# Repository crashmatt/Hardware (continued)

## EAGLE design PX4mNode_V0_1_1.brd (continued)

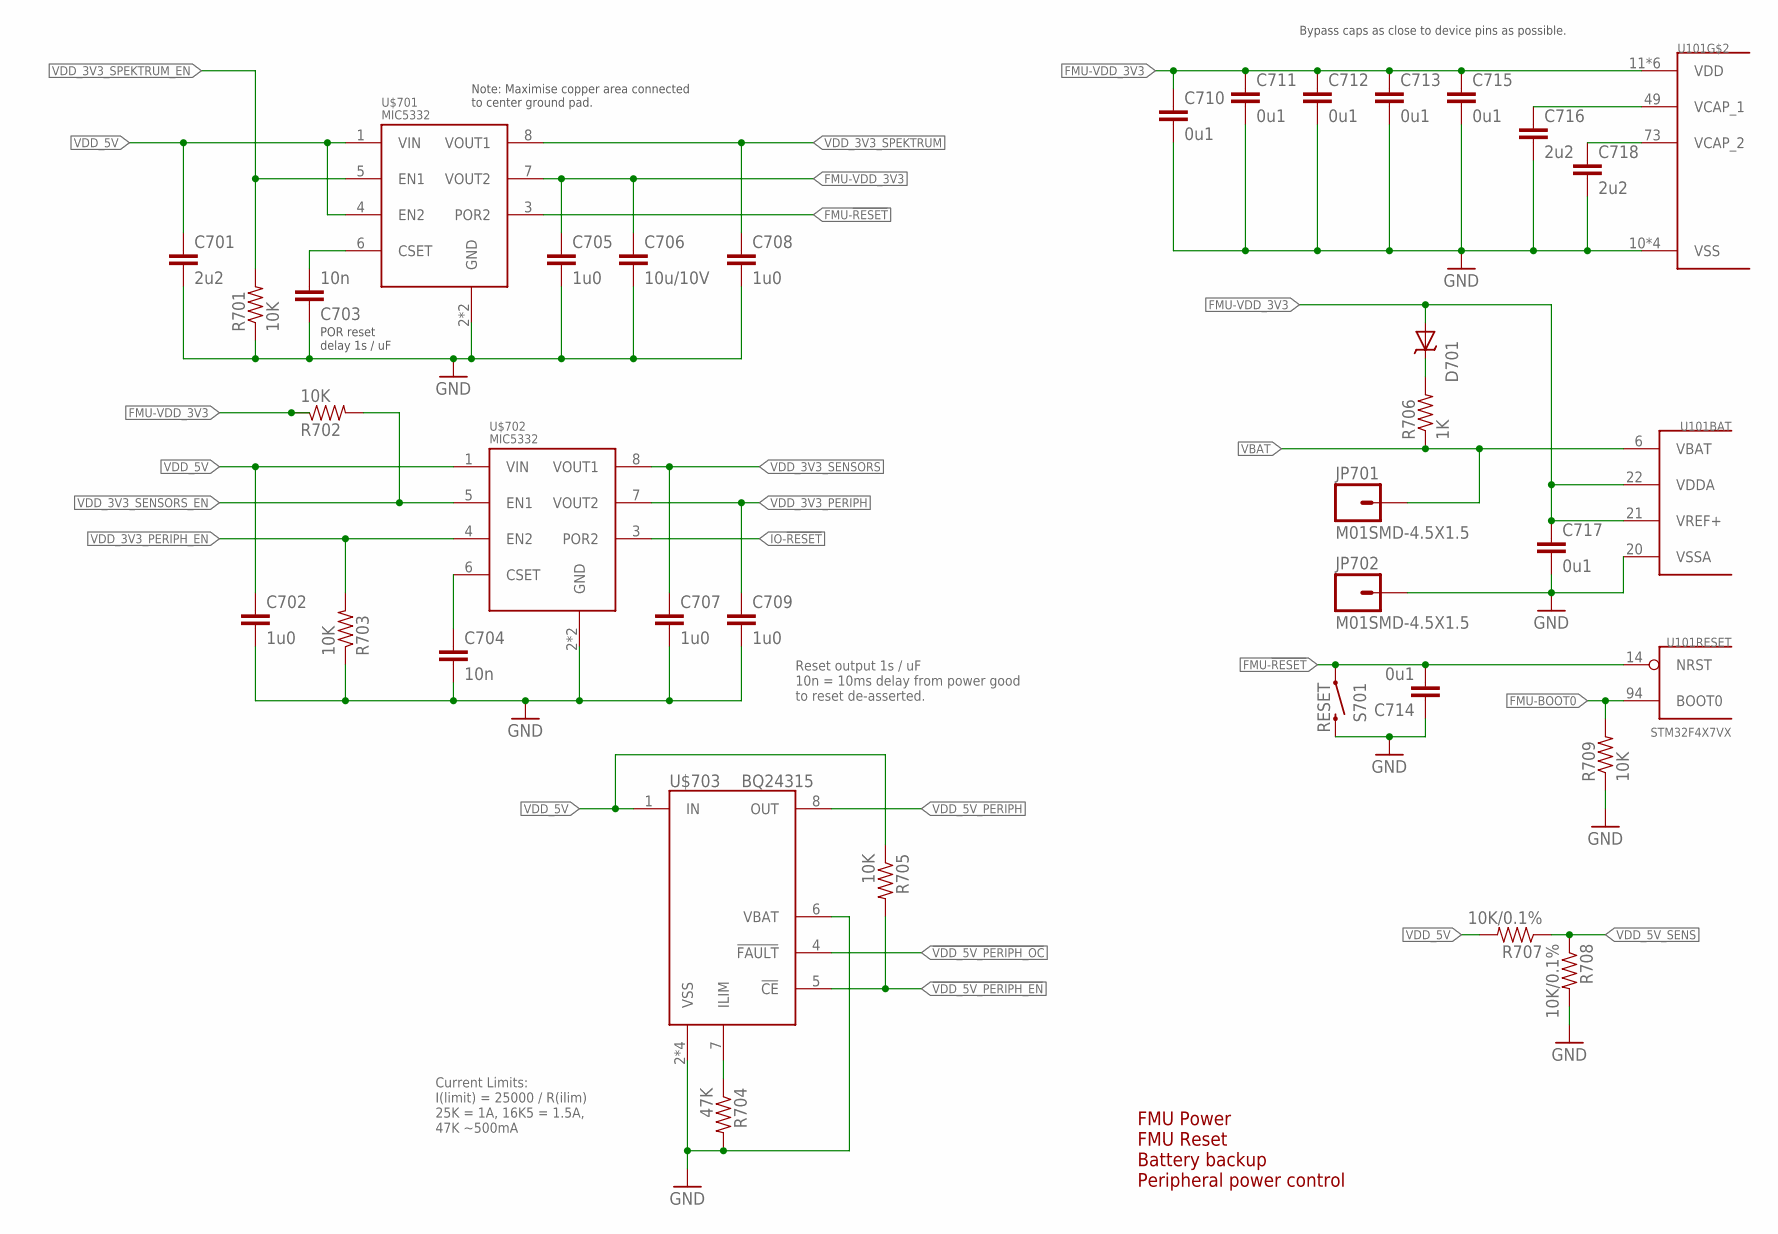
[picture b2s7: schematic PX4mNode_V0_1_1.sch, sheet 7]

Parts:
C701, C716, C718: 2u2; 0603-CAP; PARTNO C1608Y5V1C225Z
C702, C705, C707, C708, C709: 1u0; 0603-CAP; PARTNO CC0603ZRY5V7BB105
C703, C704: 10n; 0402-CAP; PARTNO CC0402KRX7R7BB103
C706: 10u/10V; 0805-CAP; PARTNO CC0805ZKY5V6BB106
C710, C711, C712, C713, C714, C715, C717: 0u1; 0402-CAP; PARTNO CC0402ZRY5V7BB104
D701: MSS1P4-M3; MICROSMP; PARTNO MSS1P4-M3/89A
JP701, JP702: M01SMD-4.5X1.5; PAD-1.5X4.5
R701, R702, R703, R705, R709: 10K; 0402-RES; PARTNO RC0402FR-0710KL
R704: 47K; 0402-RES; PARTNO RMCF0402FT47K
R706: 1K; 0402-RES; PARTNO RC0402FR-071KL
R707, R708: 10K/0.1%; 0402-RES; PARTNO ERA-2AEB103X
S701: RESET; EVQP7J01K; PARTNO EVQP7J01K
U101: STM32F4X7VX; TQFP100; PARTNO STM32F427VI
U$701, U$702: MIC5332; MLF-8-EPAD; PARTNO MIC5332-SSYMT
U$703: BQ24315; QFN8-DSG; PARTNO BQ24315DSGR

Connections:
!VDD_5V_PERIPH_EN: R705.P$2 (2), U$703.5 (!CE); also elsewhere on the board
!VDD_5V_PERIPH_OC: U$703.4 (!FAULT); also elsewhere on the board
FMU-!RESET: C714.P$2 (2), S701.A1 (1), U101.14 (NRST), U$701.3 (POR2); also elsewhere on the board
FMU-BOOT0: R709.P$2 (2), U101.94 (BOOT0); also elsewhere on the board
FMU-VDD_3V3: C705.P$1 (1), C706.P$1 (1), C710.P$1 (1), C711.P$1 (1), C712.P$1 (1), C713.P$1 (1), C715.P$1 (1), C717.P$1 (1), D701.ANODE (A), R702.P$1 (1), U101.11 (VDD), U101.19 (VDD), U101.21 (VREF+), U101.22 (VDDA), U101.28 (VDD), U101.50 (VDD), U101.75 (VDD), U101.100 (VDD), U$701.7 (VOUT2); also elsewhere on the board
GND: C701.P$2 (2), C702.P$2 (2), C703.P$1 (1), C704.P$2 (2), C705.P$2 (2), C706.P$2 (2), C707.P$2 (2), C708.P$2 (2), C709.P$2 (2), C710.P$2 (2), C711.P$2 (2), C712.P$2 (2), C713.P$2 (2), C714.P$1 (1), C715.P$2 (2), C716.P$2 (2), C717.P$2 (2), C718.P$2 (2), JP702.P$1, R701.P$1 (1), R703.P$1 (1), R704.P$2 (2), R708.P$2 (2), R709.P$1 (1), S701.B3 (2), U101.10 (VSS), U101.20 (VSSA), U101.27 (VSS), U101.74 (VSS), U101.99 (VSS), U$701.2 (GND), U$701.GND, U$702.2 (GND), U$702.GND, U$703.2 (VSS), U$703.6 (VBAT), U$703.GND (VSS), U$703.P$2 (VSS), U$703.P$3 (VSS); also elsewhere on the board
IO-!RESET: U$702.3 (POR2)
unnamed: C718.P$1 (1), U101.73 (VCAP_2)
unnamed: D701.CATHODE (C), R706.P$2 (2)
unnamed: C703.P$2 (2), U$701.6 (CSET)
unnamed: C716.P$1 (1), U101.49 (VCAP_1)
unnamed: R704.P$1 (1), U$703.7 (ILIM)
unnamed: C704.P$1 (1), U$702.6 (CSET)
VBAT: JP701.P$1, R706.P$1 (1), U101.6 (VBAT)
VDD_3V3_PERIPH: C709.P$1 (1), U$702.7 (VOUT2)
VDD_3V3_PERIPH_EN: R703.P$2 (2), U$702.4 (EN2)
VDD_3V3_SENSORS: C707.P$1 (1), U$702.8 (VOUT1); also elsewhere on the board
VDD_3V3_SENSORS_EN: R702.P$2 (2), U$702.5 (EN1); also elsewhere on the board
VDD_3V3_SPEKTRUM: C708.P$1 (1), U$701.8 (VOUT1); also elsewhere on the board
VDD_3V3_SPEKTRUM_EN: R701.P$2 (2), U$701.5 (EN1); also elsewhere on the board
VDD_5V: C701.P$1 (1), C702.P$1 (1), R705.P$1 (1), R707.P$2 (2), U$701.1 (VIN), U$701.4 (EN2), U$702.1 (VIN), U$703.1 (IN); also elsewhere on the board
VDD_5V_PERIPH: U$703.8 (OUT); also elsewhere on the board
VDD_5V_SENS: R707.P$1 (1), R708.P$1 (1); also elsewhere on the board

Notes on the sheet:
FMU Power FMU Reset Battery backup Peripheral power control
Bypass caps as close to device pins as possible.
Note: Maximise copper area connected to center ground pad.
POR reset delay 1s / uF
Current Limits: I(limit) = 25000 / R(ilim) 25K = 1A, 16K5 = 1.5A, 47K ~500mA
Reset output 1s / uF 10n = 10ms delay from power good to reset de-asserted.

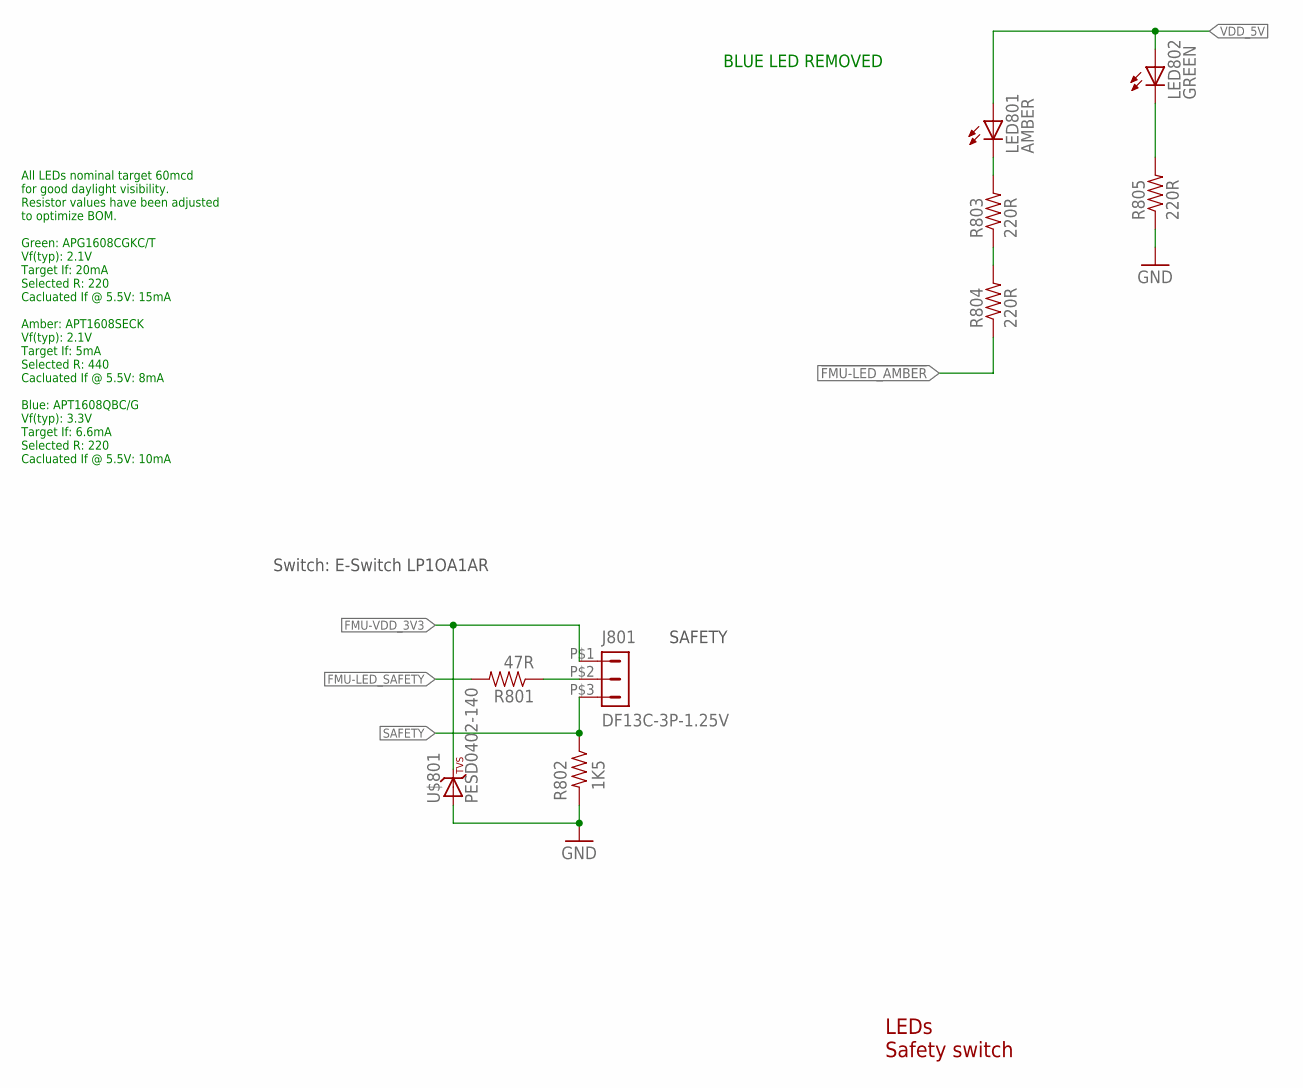
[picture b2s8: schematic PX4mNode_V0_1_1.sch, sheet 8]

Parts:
J801: DF13C-3P-1.25V; PARTNO DF13C-3P-1.25V(20)
LED801: AMBER; 0603-LED; PARTNO APTD1608SECK
LED802: GREEN; 0603-LED; PARTNO APTD1608CGCK
R801: 47R; 0402-RES; PARTNO RC0402JR-0747RL
R802: 1K5; 0402-RES; PARTNO RC0402FR-071K5L
R803, R804, R805: 220R; 0402-RES; PARTNO RC0402FR-07220RL
U$801: PESD0402-140; 0402-TVS; PARTNO PESD0402-140

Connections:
!FMU-LED_AMBER: R804.P$1 (1); also elsewhere on the board
FMU-LED_SAFETY: R801.P$2 (2)
FMU-VDD_3V3: J801.P$1 (1), U$801.C; also elsewhere on the board
GND: R802.P$2 (2), R805.P$1 (1), U$801.A; also elsewhere on the board
unnamed: LED802.C, R805.P$2 (2)
unnamed: R803.P$1 (1), R804.P$2 (2)
unnamed: LED801.C, R803.P$2 (2)
unnamed: J801.P$2 (2), R801.P$1 (1)
SAFETY: J801.P$3 (3), R802.P$1 (1)
VDD_5V: LED801.A, LED802.A; also elsewhere on the board

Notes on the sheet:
LEDs Safety switch
Switch: E-Switch LP1OA1AR
SAFETY
All LEDs nominal target 60mcd for good daylight visibility. Resistor values have been adjusted to optimize BOM. Green: APG1608CGKC/T Vf(typ): 2.1V Target If: 20mA Selected R: 220 Cacluated If @ 5.5V: 15mA Amber: APT1608SECK Vf(typ): 2.1V Target If: 5mA Selected R: 440 Cacluated If @ 5.5V: 8mA Blue: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
BLUE LED REMOVED

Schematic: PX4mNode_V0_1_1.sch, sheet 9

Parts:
D901: DIODESOD; SOD-323
D902, D903: B340A; SMA-DIODE; PARTNO B340A
D904: MSS1P4-M3; MICROSMP; PARTNO MSS1P4-M3/89A
JP901: M02PTH3; 1X02_LONGPADS
R901, R902, R903: 10K/0.1%; 0402-RES; PARTNO ERA-2AEB103X

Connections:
GND: D901.2 (A), JP901.2, R903.P$1 (1); also elsewhere on the board
unnamed: D901.1 (C), R901.P$1 (1), R902.P$2 (2)
VBUS: D904.ANODE (A); also elsewhere on the board
VDD_IN: D902.C, D903.C, D904.CATHODE (C); also elsewhere on the board
VDD_SERVO_SENS: R902.P$1 (1), R903.P$2 (2)
V_EXT: D903.A, JP901.1, R901.P$2 (2)
V_SERVO: D902.A; also elsewhere on the board

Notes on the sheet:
IO SoC Ports Spektrum/DSM port
Timer allocation: PA0: TIM2_CH1: IO-CH1 PA1: TIM2_CH2: IO-CH2 PB8: TIM4_CH3: IO-CH3 PB9: TIM4_CH4: IO-CH4 PA6: TIM3_CH1: IO-CH5 PA7: TIM3_CH2: IO-CH6 PB0: TIM3_CH3: IO-CH7 PB1: TIM3_CH4: IO-CH8 PA8: TIM1_CH1: PPM_IN PA11: TIM1_CH4: RSSI_IN
DO NOT FIT

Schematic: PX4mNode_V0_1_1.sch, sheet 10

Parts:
J1001: SERVO_HEADER-3X8; 3X8RA_SERVO
JP1001, JP1002: M01SMD-4.5X1.5; PAD-1.5X4.5
L1001: NUF8402MN; DFN16-THIN
R1001, R1002: 220R; 0402-RES; PARTNO RC0402FR-07220RL

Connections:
FMU-CH1: L1001.P$1; also elsewhere on the board
FMU-CH1-PROT: J1001.S1, L1001.P$16
FMU-CH2: L1001.P$2; also elsewhere on the board
FMU-CH3: L1001.P$3; also elsewhere on the board
FMU-CH4: L1001.P$4; also elsewhere on the board
FMU-CH5: L1001.P$5; also elsewhere on the board
FMU-CH6: L1001.P$6; also elsewhere on the board
FMU-CH7: L1001.P$7; also elsewhere on the board
FMU-CH8: L1001.P$8; also elsewhere on the board
FMU-CH9: R1001.P$2 (2); also elsewhere on the board
FMU-CH10: R1002.P$2 (2); also elsewhere on the board
GND: J1001.GND_S1, J1001.GND_S2, J1001.GND_S3, J1001.GND_S4, J1001.GND_S5, J1001.GND_S6, J1001.GND_S7, J1001.GND_S8, L1001.P$EP (GND); also elsewhere on the board
unnamed: J1001.S8, L1001.P$9
unnamed: J1001.S7, L1001.P$10
unnamed: JP1001.P$1, R1001.P$1 (1)
unnamed: JP1002.P$1, R1002.P$1 (1)
unnamed: J1001.S6, L1001.P$11
unnamed: J1001.S5, L1001.P$12
unnamed: J1001.S4, L1001.P$13
unnamed: J1001.S3, L1001.P$14
unnamed: J1001.S2, L1001.P$15
V_SERVO: J1001.PWR_S1, J1001.PWR_S2, J1001.PWR_S3, J1001.PWR_S4, J1001.PWR_S5, J1001.PWR_S6, J1001.PWR_S7, J1001.PWR_S8; also elsewhere on the board

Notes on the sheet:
Servo Header S.Bus interface
Servo outputs

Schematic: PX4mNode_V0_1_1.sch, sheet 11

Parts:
BOOT: PAD.04; PAD.04X.04; PARTNO *
JP1101, JP1102, JP1103, JP1104: FIDUCIAL1.5X3; FIDUCIAL-1.5X3; PARTNO *
M3_MOUNT1101, M3_MOUNT1102, M3_MOUNT1103, M3_MOUNT1104: MOUNT-HOLE3.1MM; MOUNT-HOLE3.1; PARTNO *
OSHW_LOGO: OSHW-LOGOS; OSHW-LOGO-S; PARTNO *

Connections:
FMU-BOOT0: BOOT.P$1; also elsewhere on the board

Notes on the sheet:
Mounting holes to suit M3 fastener
and Richco R908 series spacer.
Use R908-5 spacers to stack with
other PX4 series boards (7.95 mm).
Production Testing Pads
Test and Fiducials
Minimum drill: 0.3 mm
Minimum trace width (use mm for traces): 0.15 mm
Minimum copper distance (all signals): 0.15 mm
Dimension / hole minimum distance: 0.2 mm
Layout grid: 4 mil, part grid: 4 mil. Dimensions / hole positions: 0.5 mm
Board: FR4 black, 1.0 mm. Solder stop on vias < 0.6 mm.
Signoff rules: Footprint checked, pinmap checked, schematic checked, cross-references to other pages checked.
Routing: 1: general/escape 2: ground 3: horizontal 4: vertical 5: power 6: general/escape
Fiducials for machine vision alignment.

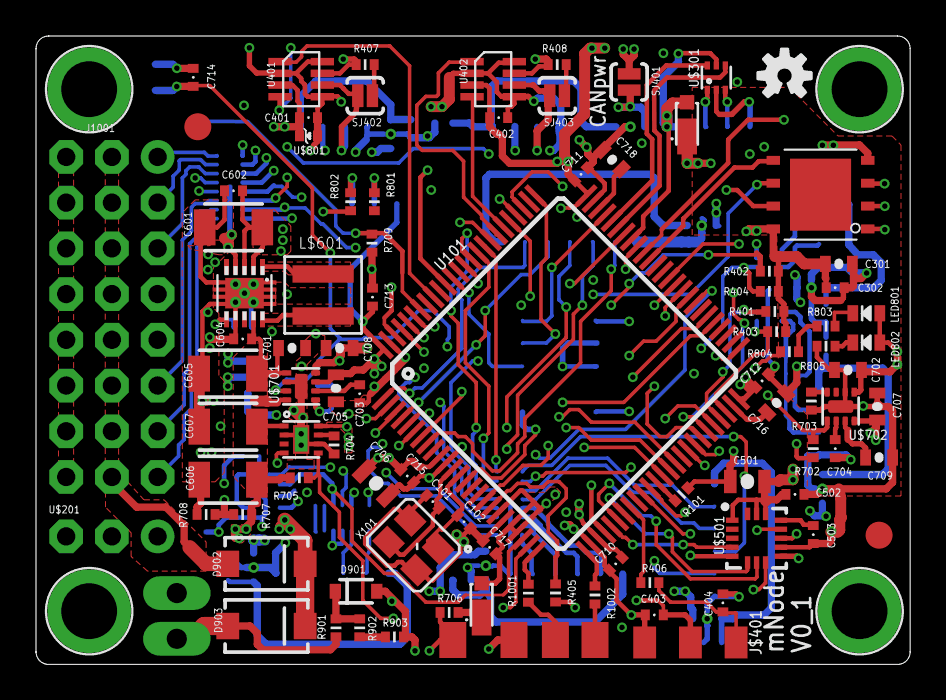
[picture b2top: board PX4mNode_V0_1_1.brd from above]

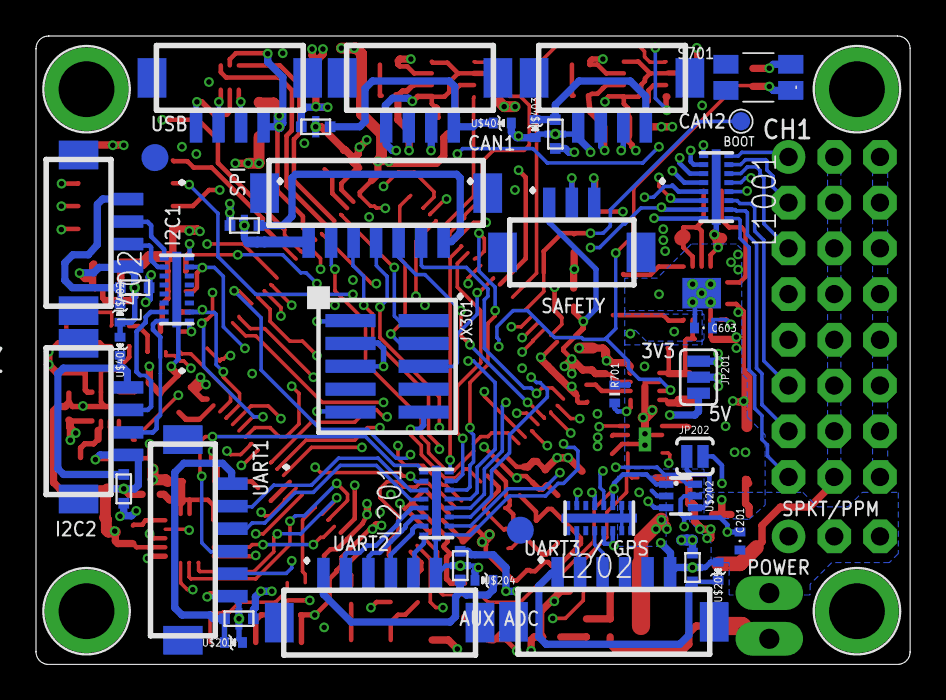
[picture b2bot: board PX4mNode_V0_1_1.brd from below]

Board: 6 copper layers, 48.6 x 34.9 mm, 140 parts (40 on the bottom side), 144 nets.

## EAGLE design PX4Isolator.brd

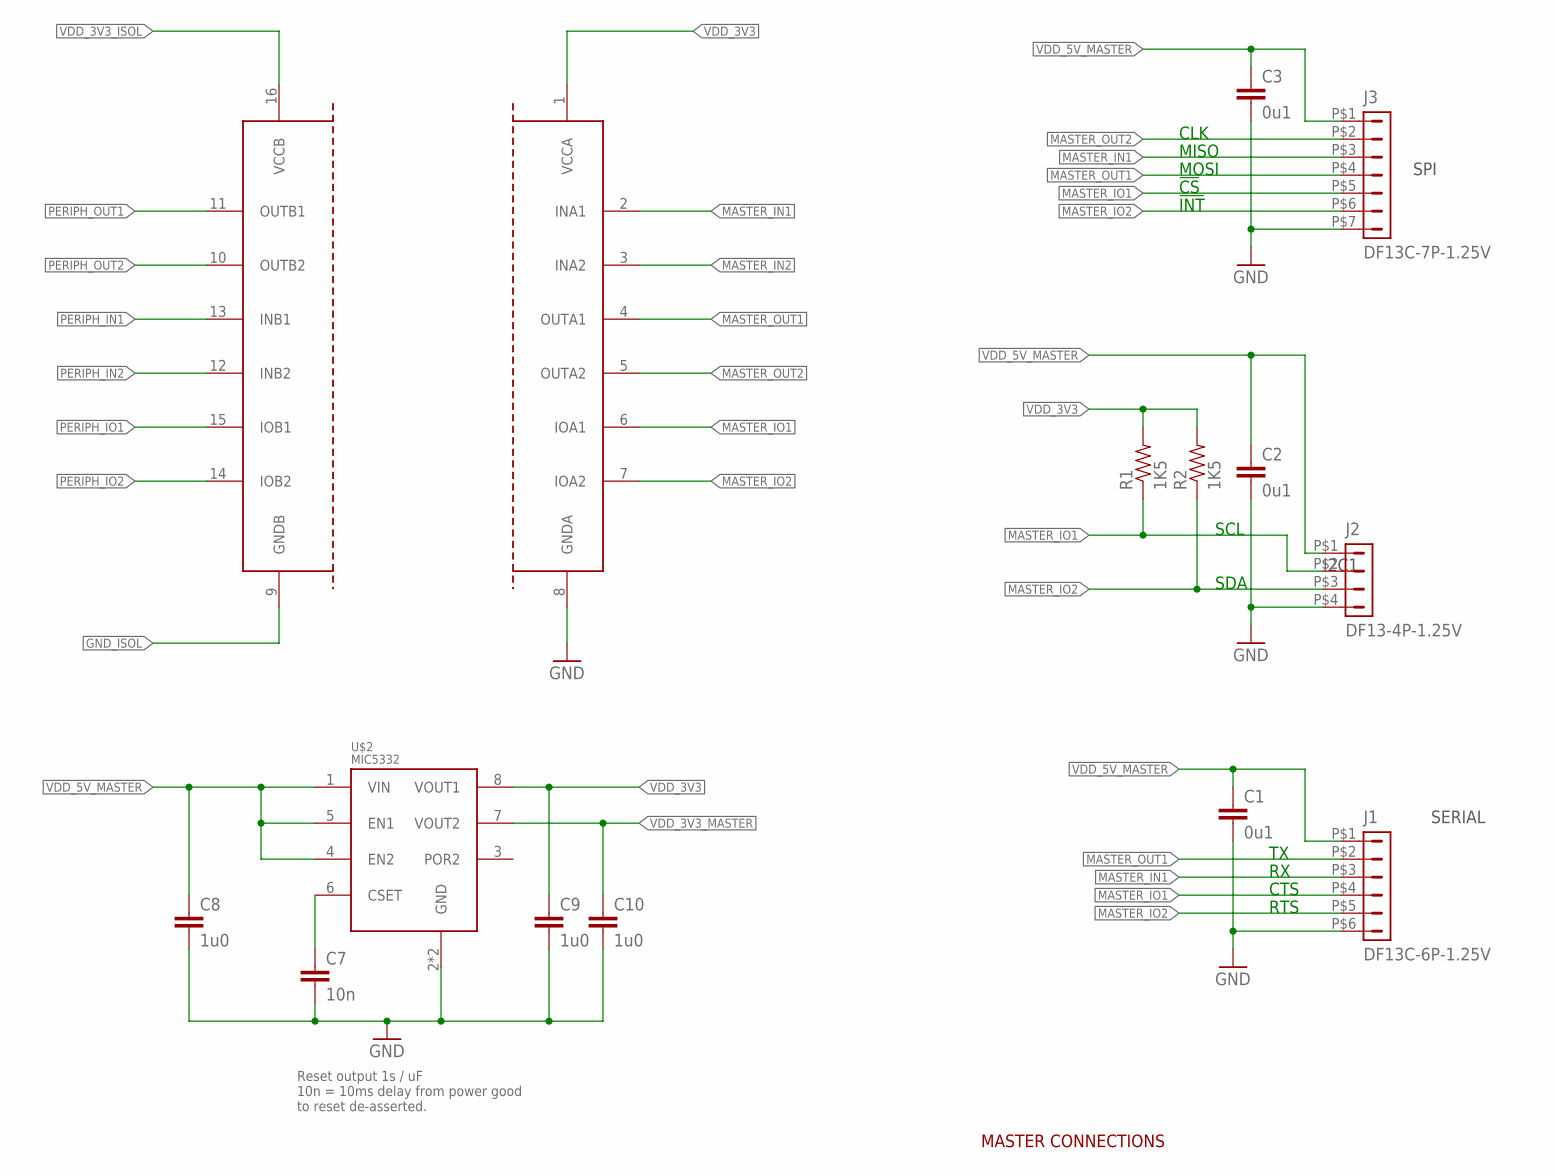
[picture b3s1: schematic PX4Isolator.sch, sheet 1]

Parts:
C1, C2, C3: 0u1; 0402-CAP; PARTNO CC0402ZRY5V7BB104
C7: 10n; 0402-CAP; PARTNO CC0402KRX7R7BB103
C8, C9, C10: 1u0; 0603-CAP; PARTNO CC0603ZRY5V7BB105
J1: DF13C-6P-1.25V; PARTNO DF13C-6P-1.25V(20)
J2: DF13-4P-1.25V; DF13C-4P-1.25V; PARTNO DF13C-4P-1.25V(20)
J3: DF13C-7P-1.25V; PARTNO DF13C-7P-1.25V(20)
R1, R2: 1K5; 0402-RES; PARTNO RC0402FR-071K5L
U$1: MAX14850; SOIC16
U$2: MIC5332; MLF-8-EPAD; PARTNO MIC5332-SSYMT

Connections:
GND: C1.P$2 (2), C2.P$2 (2), C3.P$2 (2), C7.P$2 (2), C8.P$2 (2), C9.P$2 (2), C10.P$2 (2), J1.P$6 (6), J2.P$4 (4), J3.P$7 (7), U$1.8 (GNDA), U$2.2 (GND), U$2.GND; also elsewhere on the board
GND_ISOL: U$1.9 (GNDB); also elsewhere on the board
MASTER_IN1: J1.P$3 (3), J3.P$3 (3), U$1.2 (INA1)
MASTER_IN2: U$1.3 (INA2)
MASTER_IO1: J1.P$4 (4), J2.P$2 (2), J3.P$5 (5), R1.P$1 (1), U$1.6 (IOA1)
MASTER_IO2: J1.P$5 (5), J2.P$3 (3), J3.P$6 (6), R2.P$1 (1), U$1.7 (IOA2)
MASTER_OUT1: J1.P$2 (2), J3.P$4 (4), U$1.4 (OUTA1)
MASTER_OUT2: J3.P$2 (2), U$1.5 (OUTA2)
unnamed: C7.P$1 (1), U$2.6 (CSET)
PERIPH_IN1: U$1.13 (INB1); also elsewhere on the board
PERIPH_IN2: U$1.12 (INB2)
PERIPH_IO1: U$1.15 (IOB1); also elsewhere on the board
PERIPH_IO2: U$1.14 (IOB2); also elsewhere on the board
PERIPH_OUT1: U$1.11 (OUTB1); also elsewhere on the board
PERIPH_OUT2: U$1.10 (OUTB2); also elsewhere on the board
VDD_3V3: C9.P$1 (1), R1.P$2 (2), R2.P$2 (2), U$1.1 (VCCA), U$2.8 (VOUT1); also elsewhere on the board
VDD_3V3_ISOL: U$1.16 (VCCB); also elsewhere on the board
VDD_3V3_MASTER: C10.P$1 (1), U$2.7 (VOUT2)
VDD_5V_MASTER: C1.P$1 (1), C2.P$1 (1), C3.P$1 (1), C8.P$1 (1), J1.P$1 (1), J2.P$1 (1), J3.P$1 (1), U$2.1 (VIN), U$2.4 (EN2), U$2.5 (EN1)

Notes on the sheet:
SPI
MASTER CONNECTIONS
I2C1
SERIAL
CLK
MISO
MOSI
!CS
!INT
SCL
SDA
CTS
RTS
Reset output 1s / uF 10n = 10ms delay from power good to reset de-asserted.

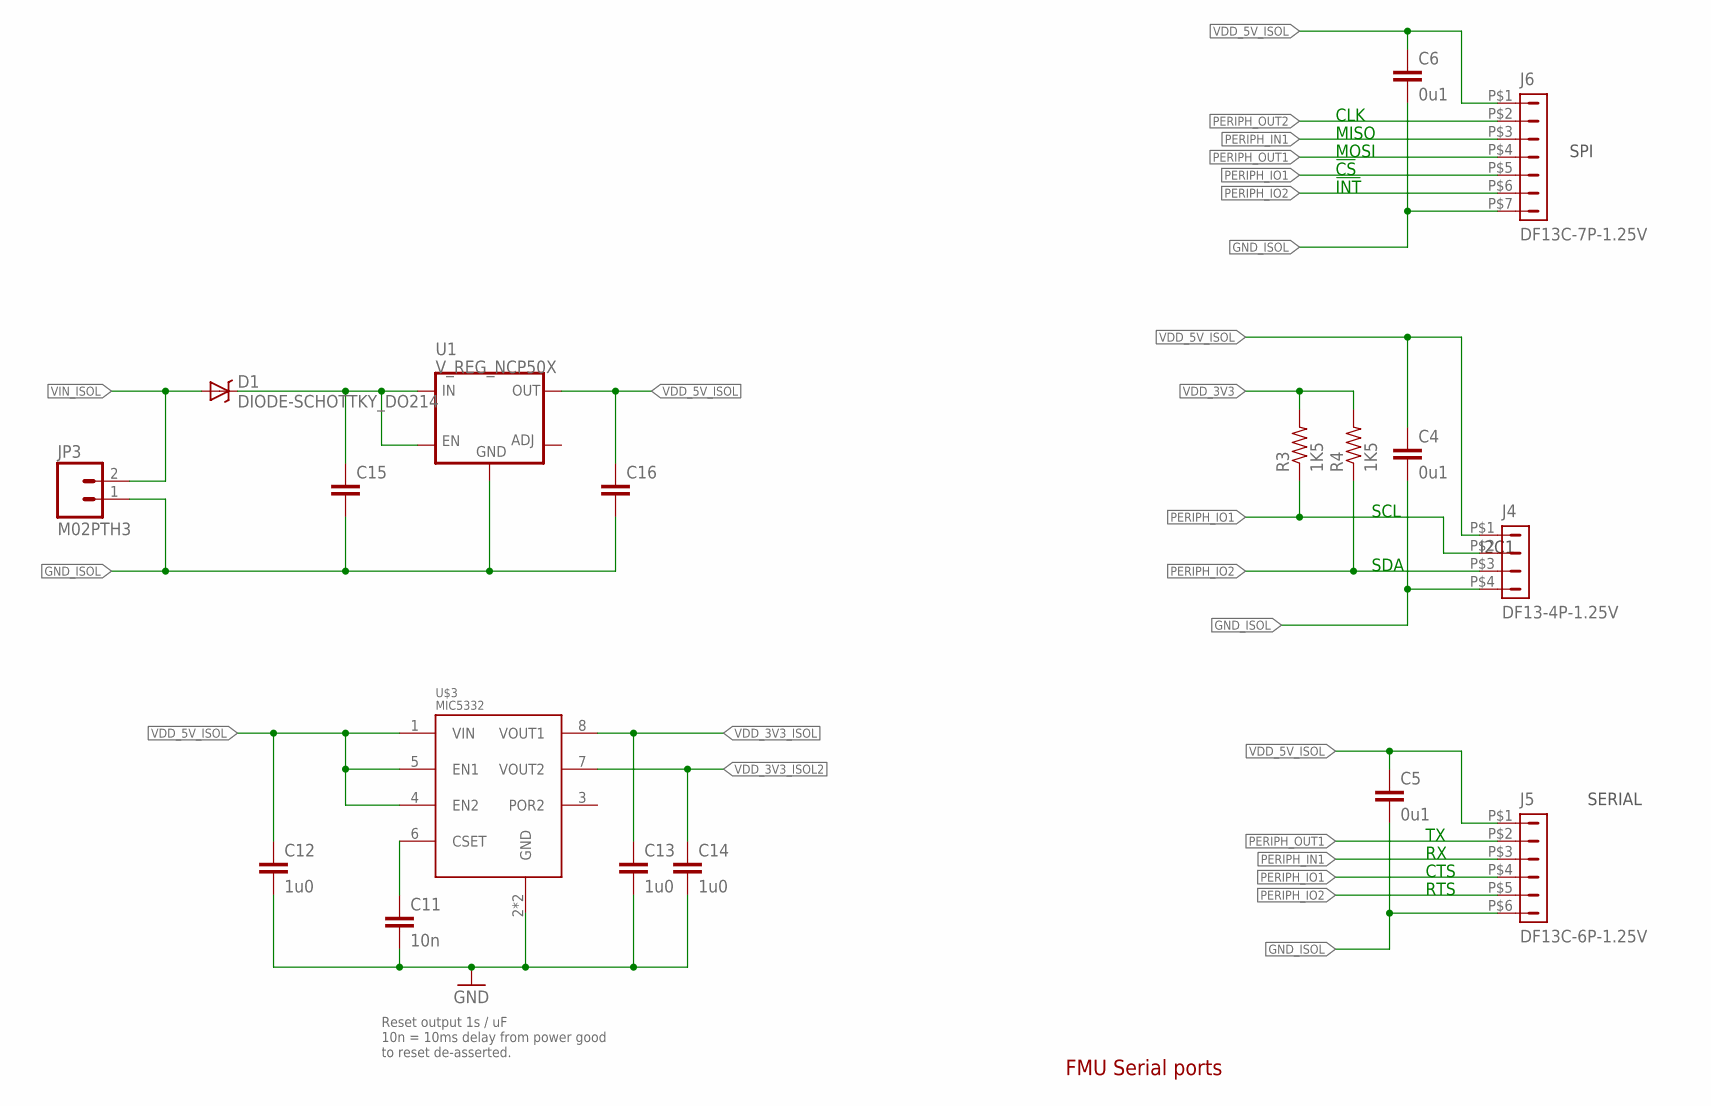
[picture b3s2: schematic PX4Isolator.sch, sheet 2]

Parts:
C4, C5, C6: 0u1; 0402-CAP; PARTNO CC0402ZRY5V7BB104
C11: 10n; 0402-CAP; PARTNO CC0402KRX7R7BB103
C12, C13, C14: 1u0; 0603-CAP; PARTNO CC0603ZRY5V7BB105
C15, C16: CAP0603; 0603-CAP
D1: DIODE-SCHOTTKY_DO214; DO214AC
J4: DF13-4P-1.25V; DF13C-4P-1.25V; PARTNO DF13C-4P-1.25V(20)
J5: DF13C-6P-1.25V; PARTNO DF13C-6P-1.25V(20)
J6: DF13C-7P-1.25V; PARTNO DF13C-7P-1.25V(20)
JP3: M02PTH3; 1X02_LONGPADS
R3, R4: 1K5; 0402-RES; PARTNO RC0402FR-071K5L
U1: V_REG_NCP50X; DPAK-5
U$3: MIC5332; MLF-8-EPAD; PARTNO MIC5332-SSYMT

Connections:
GND: C11.P$2 (2), C12.P$2 (2), C13.P$2 (2), C14.P$2 (2), U$3.2 (GND), U$3.GND; also elsewhere on the board
GND_ISOL: C4.P$2 (2), C5.P$2 (2), C6.P$2 (2), C15.P$2 (2), C16.P$2 (2), J4.P$4 (4), J5.P$6 (6), J6.P$7 (7), JP3.1, U1.GND; also elsewhere on the board
unnamed: C11.P$1 (1), U$3.6 (CSET)
unnamed: C15.P$1 (1), D1.C, U1.EN, U1.VIN (IN)
PERIPH_IN1: J5.P$3 (3), J6.P$3 (3); also elsewhere on the board
PERIPH_IO1: J4.P$2 (2), J5.P$4 (4), J6.P$5 (5), R3.P$1 (1); also elsewhere on the board
PERIPH_IO2: J4.P$3 (3), J5.P$5 (5), J6.P$6 (6), R4.P$1 (1); also elsewhere on the board
PERIPH_OUT1: J5.P$2 (2), J6.P$4 (4); also elsewhere on the board
PERIPH_OUT2: J6.P$2 (2); also elsewhere on the board
VDD_3V3: R3.P$2 (2), R4.P$2 (2); also elsewhere on the board
VDD_3V3_ISOL: C13.P$1 (1), U$3.8 (VOUT1); also elsewhere on the board
VDD_3V3_ISOL2: C14.P$1 (1), U$3.7 (VOUT2)
VDD_5V_ISOL: C4.P$1 (1), C5.P$1 (1), C6.P$1 (1), C12.P$1 (1), C16.P$1 (1), J4.P$1 (1), J5.P$1 (1), J6.P$1 (1), U1.VOUT (OUT), U$3.1 (VIN), U$3.4 (EN2), U$3.5 (EN1)
VIN_ISOL: D1.A, JP3.2

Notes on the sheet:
FMU Serial ports
SPI
I2C1
SERIAL
CLK
MISO
MOSI
!CS
!INT
SCL
SDA
CTS
RTS
Reset output 1s / uF 10n = 10ms delay from power good to reset de-asserted.

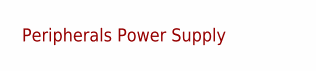
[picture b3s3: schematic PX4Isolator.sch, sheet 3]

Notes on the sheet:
Peripherals Power Supply

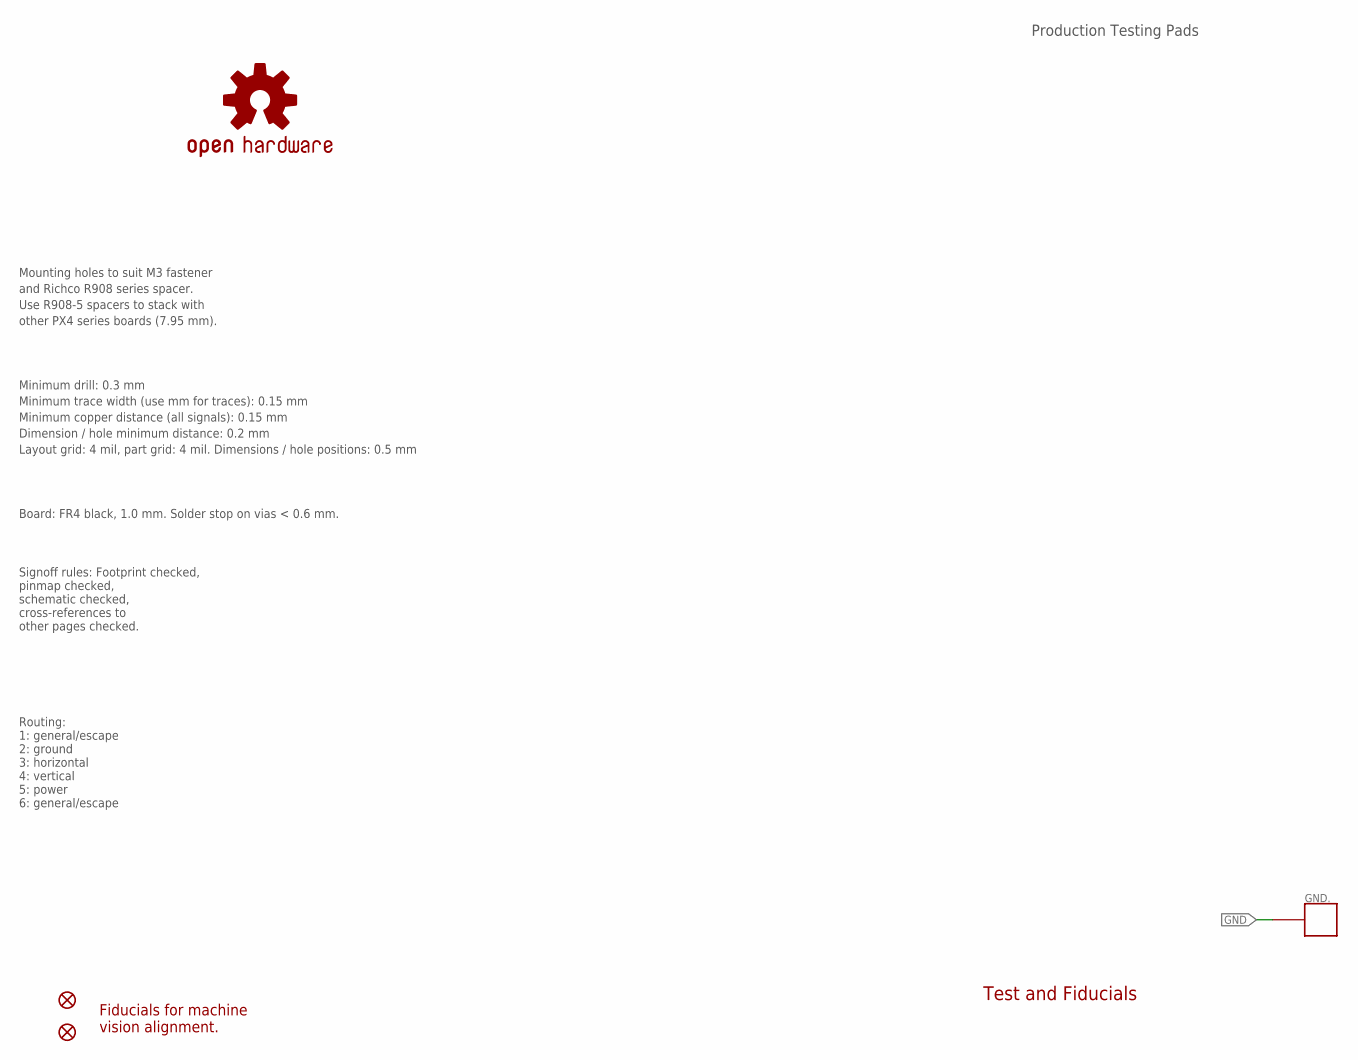
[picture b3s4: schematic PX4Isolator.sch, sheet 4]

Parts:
GND.: PAD.04; PAD.04X.04; PARTNO *
JP1, JP2: FIDUCIAL1.5X3; FIDUCIAL-1.5X3; PARTNO *
OSHW_LOGO: OSHW-LOGOS; OSHW-LOGO-S; PARTNO *

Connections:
GND: GND..P$1; also elsewhere on the board

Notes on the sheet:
Mounting holes to suit M3 fastener
and Richco R908 series spacer.
Use R908-5 spacers to stack with
other PX4 series boards (7.95 mm).
Production Testing Pads
Test and Fiducials
Minimum drill: 0.3 mm
Minimum trace width (use mm for traces): 0.15 mm
Minimum copper distance (all signals): 0.15 mm
Dimension / hole minimum distance: 0.2 mm
Layout grid: 4 mil, part grid: 4 mil. Dimensions / hole positions: 0.5 mm
Board: FR4 black, 1.0 mm. Solder stop on vias < 0.6 mm.
Signoff rules: Footprint checked, pinmap checked, schematic checked, cross-references to other pages checked.
Routing: 1: general/escape 2: ground 3: horizontal 4: vertical 5: power 6: general/escape
Fiducials for machine vision alignment.

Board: 6 copper layers, 36 parts (10 on the bottom side), 22 nets, no tracks yet.

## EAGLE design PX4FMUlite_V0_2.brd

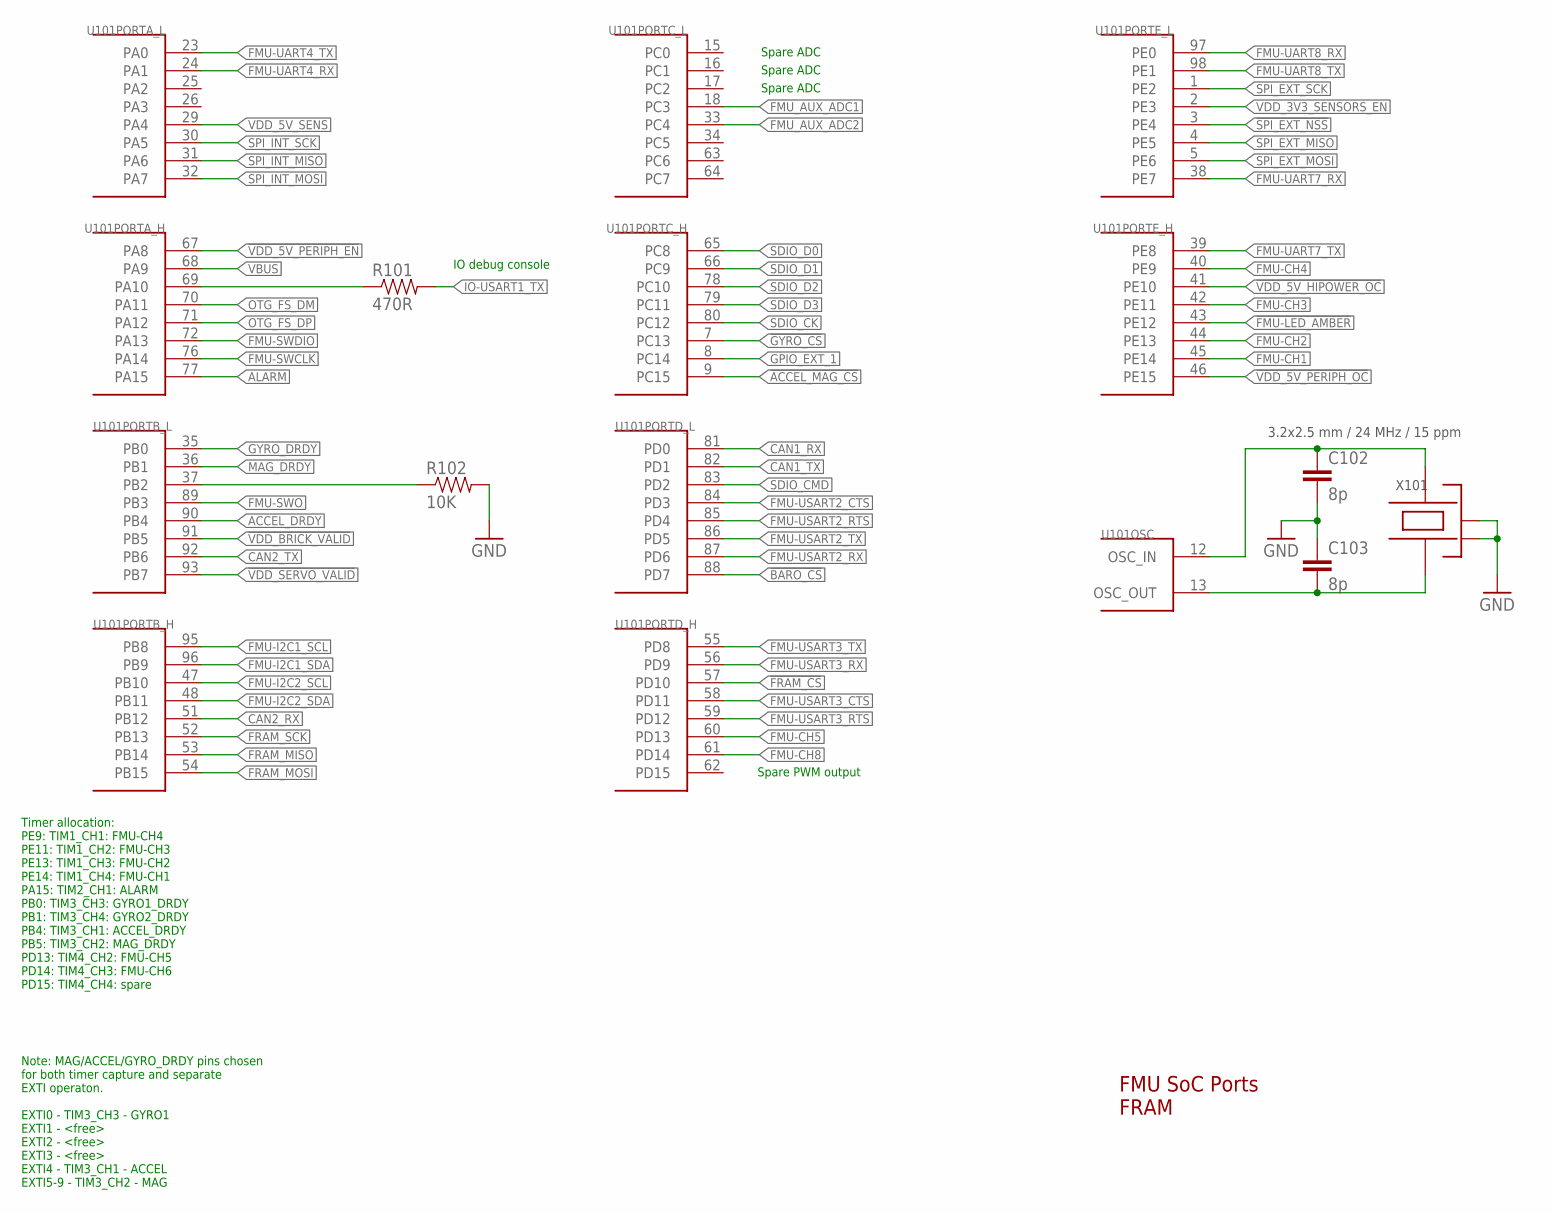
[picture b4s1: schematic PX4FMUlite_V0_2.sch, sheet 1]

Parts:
C102, C103: 8p; 0402-CAP; PARTNO C1005C0G1H080C
R101: 470R; 0402-RES; PARTNO RC0402FR-07470RL
R102: 10K; 0402-RES; PARTNO RC0402FR-0710KL
U101: STM32F4X7VX; TQFP100; PARTNO STM32F427VI
X101: 3.2x2.5 mm / 24 MHz / 15 ppm; OSCILLATOR-3.2X2.5; PARTNO NX3225SA-24.000000MHZ

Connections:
!ACCEL_MAG_CS: U101.9 (PC15); also elsewhere on the board
!BARO_CS: U101.88 (PD7)
!FMU-LED_AMBER: U101.43 (PE12); also elsewhere on the board
!FRAM_CS: U101.57 (PD10)
!GYRO_CS: U101.7 (PC13); also elsewhere on the board
!SPI_EXT_NSS: U101.3 (PE4); also elsewhere on the board
!VDD_5V_HIPOWER_OC: U101.41 (PE10)
!VDD_5V_PERIPH_EN: U101.67 (PA8); also elsewhere on the board
!VDD_5V_PERIPH_OC: U101.46 (PE15); also elsewhere on the board
!VDD_BRICK_VALID: U101.91 (PB5)
!VDD_SERVO_VALID: U101.93 (PB7)
ACCEL_DRDY: U101.90 (PB4); also elsewhere on the board
ALARM: U101.77 (PA15)
CAN1_RX: U101.81 (PD0); also elsewhere on the board
CAN1_TX: U101.82 (PD1); also elsewhere on the board
CAN2_RX: U101.51 (PB12); also elsewhere on the board
CAN2_TX: U101.92 (PB6); also elsewhere on the board
FMU-CH1: U101.45 (PE14); also elsewhere on the board
FMU-CH2: U101.44 (PE13); also elsewhere on the board
FMU-CH3: U101.42 (PE11); also elsewhere on the board
FMU-CH4: U101.40 (PE9); also elsewhere on the board
FMU-CH5: U101.60 (PD13); also elsewhere on the board
FMU-CH8: U101.61 (PD14); also elsewhere on the board
FMU-I2C1_SCL: U101.95 (PB8); also elsewhere on the board
FMU-I2C1_SDA: U101.96 (PB9); also elsewhere on the board
FMU-I2C2_SCL: U101.47 (PB10); also elsewhere on the board
FMU-I2C2_SDA: U101.48 (PB11); also elsewhere on the board
FMU-SWCLK: U101.76 (PA14); also elsewhere on the board
FMU-SWDIO: U101.72 (PA13); also elsewhere on the board
FMU-SWO: U101.89 (PB3); also elsewhere on the board
FMU-UART4_RX: U101.24 (PA1); also elsewhere on the board
FMU-UART4_TX: U101.23 (PA0); also elsewhere on the board
FMU-UART7_RX: U101.38 (PE7); also elsewhere on the board
FMU-UART7_TX: U101.39 (PE8); also elsewhere on the board
FMU-UART8_RX: U101.97 (PE0); also elsewhere on the board
FMU-UART8_TX: U101.98 (PE1); also elsewhere on the board
FMU-USART2_CTS: U101.84 (PD3); also elsewhere on the board
FMU-USART2_RTS: U101.85 (PD4); also elsewhere on the board
FMU-USART2_RX: U101.87 (PD6); also elsewhere on the board
FMU-USART2_TX: U101.86 (PD5); also elsewhere on the board
FMU-USART3_CTS: U101.58 (PD11); also elsewhere on the board
FMU-USART3_RTS: U101.59 (PD12); also elsewhere on the board
FMU-USART3_RX: U101.56 (PD9); also elsewhere on the board
FMU-USART3_TX: U101.55 (PD8); also elsewhere on the board
FMU_AUX_ADC1: U101.18 (PC3); also elsewhere on the board
FMU_AUX_ADC2: U101.33 (PC4); also elsewhere on the board
FRAM_MISO: U101.53 (PB14)
FRAM_MOSI: U101.54 (PB15)
FRAM_SCK: U101.52 (PB13)
GNDX: C102.P$2 (2), C103.P$1 (1), R102.P$2 (2), X101.2 (NC_2), X101.4 (NC_4); also elsewhere on the board
GPIO_EXT_1: U101.8 (PC14); also elsewhere on the board
GYRO_DRDY: U101.35 (PB0); also elsewhere on the board
IO-USART1_TX: R101.P$2 (2); also elsewhere on the board
MAG_DRDY: U101.36 (PB1); also elsewhere on the board
unnamed: C103.P$2 (2), U101.13 (OSC_OUT), X101.1
unnamed: C102.P$1 (1), U101.12 (OSC_IN), X101.3
unnamed: R101.P$1 (1), U101.69 (PA10)
OTG_FS_DM: U101.70 (PA11); also elsewhere on the board
OTG_FS_DP: U101.71 (PA12); also elsewhere on the board
PB2-BOOT1: R102.P$1 (1), U101.37 (PB2)
SDIO_CK: U101.80 (PC12); also elsewhere on the board
SDIO_CMD: U101.83 (PD2); also elsewhere on the board
SDIO_D0: U101.65 (PC8); also elsewhere on the board
SDIO_D1: U101.66 (PC9); also elsewhere on the board
SDIO_D2: U101.78 (PC10); also elsewhere on the board
SDIO_D3: U101.79 (PC11); also elsewhere on the board
SPI_EXT_MISO: U101.4 (PE5); also elsewhere on the board
SPI_EXT_MOSI: U101.5 (PE6); also elsewhere on the board
SPI_EXT_SCK: U101.1 (PE2); also elsewhere on the board
SPI_INT_MISO: U101.31 (PA6); also elsewhere on the board
SPI_INT_MOSI: U101.32 (PA7); also elsewhere on the board
SPI_INT_SCK: U101.30 (PA5); also elsewhere on the board
VBUS: U101.68 (PA9); also elsewhere on the board
VDD_3V3_SENSORS_EN: U101.2 (PE3); also elsewhere on the board
VDD_5V_SENS: U101.29 (PA4); also elsewhere on the board

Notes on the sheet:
FMU SoC Ports FRAM
Note: MAG/ACCEL/GYRO_DRDY pins chosen for both timer capture and separate EXTI operaton. EXTI0 - TIM3_CH3 - GYRO1 EXTI1 - <free> EXTI2 - <free> EXTI3 - <free> EXTI4 - TIM3_CH1 - ACCEL EXTI5-9 - TIM3_CH2 - MAG
Timer allocation: PE9: TIM1_CH1: FMU-CH4 PE11: TIM1_CH2: FMU-CH3 PE13: TIM1_CH3: FMU-CH2 PE14: TIM1_CH4: FMU-CH1 PA15: TIM2_CH1: ALARM PB0: TIM3_CH3: GYRO1_DRDY PB1: TIM3_CH4: GYRO2_DRDY PB4: TIM3_CH1: ACCEL_DRDY PB5: TIM3_CH2: MAG_DRDY PD13: TIM4_CH2: FMU-CH5 PD14: TIM4_CH3: FMU-CH6 PD15: TIM4_CH4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
Spare PWM output
IO debug console
Spare ADC
